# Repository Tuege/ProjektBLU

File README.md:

## Welcome to GitHub Pages

You can use the [editor on GitHub](https://github.com/Tuege/ProjektBLU/edit/master/README.md) to maintain and preview the content for your website in Markdown files.

Whenever you commit to this repository, GitHub Pages will run [Jekyll](https://jekyllrb.com/) to rebuild the pages in your site, from the content in your Markdown files.

### Markdown

Markdown is a lightweight and easy-to-use syntax for styling your writing. It includes conventions for

```markdown
Syntax highlighted code block

# Header 1
## Header 2
### Header 3

- Bulleted
- List

1. Numbered
2. List

**Bold** and _Italic_ and `Code` text

[Link](url) and 
```

For more details see [GitHub Flavored Markdown](https://guides.github.com/features/mastering-markdown/).

### Jekyll Themes

Your Pages site will use the layout and styles from the Jekyll theme you have selected in your [repository settings](https://github.com/Tuege/ProjektBLU/settings). The name of this theme is saved in the Jekyll `_config.yml` configuration file.

### Support or Contact

Having trouble with Pages? Check out our [documentation](https://help.github.com/categories/github-pages-basics/) or [contact support](https://github.com/contact) and we’ll help you sort it out.

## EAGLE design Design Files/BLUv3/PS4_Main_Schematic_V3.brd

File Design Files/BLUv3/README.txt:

This Folder contains the Design files and technical documentation for the BLUv3

This board has been designed to replace the JDM-055 in the PS4 controller and can be programmed using Atmel Studio.
The microcontroller on this board is an ATxmega128A1U and the board also features an integrated esp32 module.

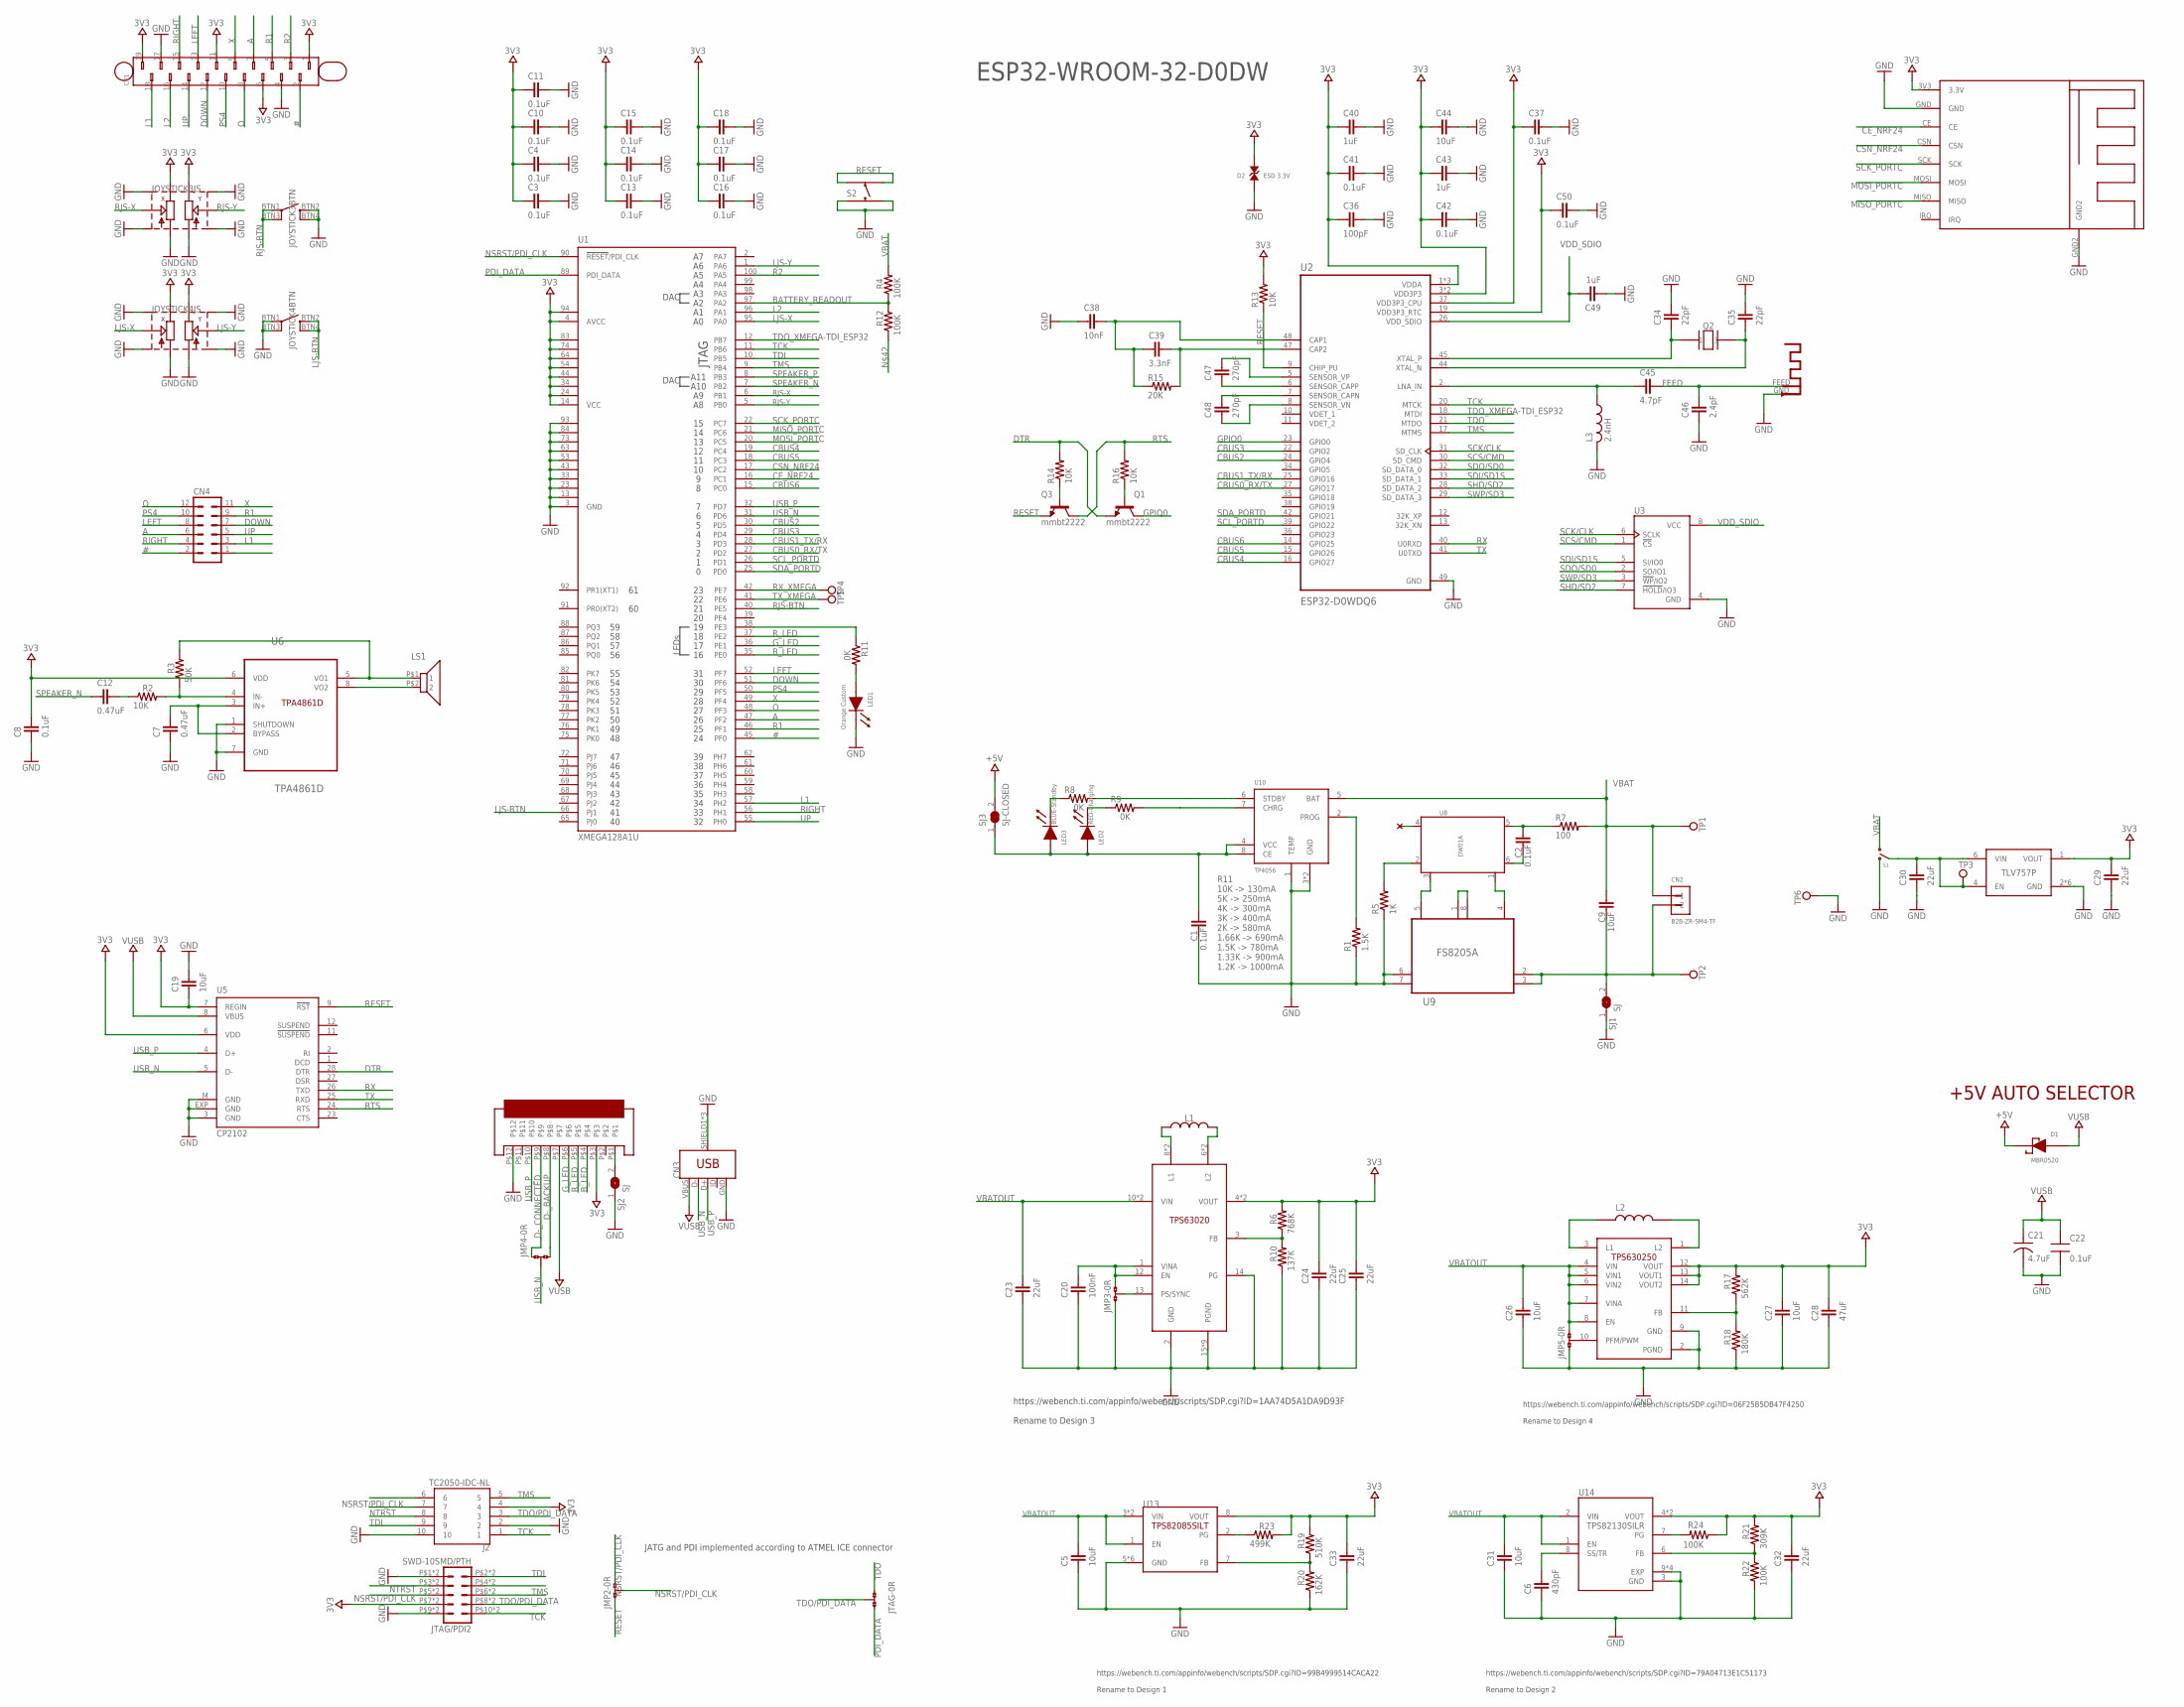
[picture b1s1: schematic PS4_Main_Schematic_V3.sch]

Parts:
ANT1: ESP32-ANTENNA; ESP32-ANT
C1: 0.1uF; C0402
C2: 0.1uF; C0603
C3, C4, C10, C11, C13, C14, C15, C16, C17, C18, C37, C41, C42, C50: 0.1uF; CAPC1005X60N
C5, C19, C26, C27, C31, C44: 10uF; CAPC1608X85N
C6: 430pF; CAPC1608X85N
C7, C12: 0.47uF; CAPC1608X85N
C8: 0.1uF; CAPC1608X85N
C9: 10uF; C0603
C20: 100nF; CAPC1608X85N
C21: 4.7uF; TAN-A
C22: 0.1uF; CAP0805-NP
C23, C24, C25, C29, C30, C32, C33: 22uF; CAPC1608X85N
C28: 47uF; 0805
C34, C35: 22pF; CAPC1005X60N
C36: 100pF; CAPC1005X60N
C38: 10nF; CAPC1005X60N
C39: 3.3nF; CAPC1005X60N
C40, C43, C49: 1uF; CAPC1005X60N
C45: 4.7pF; CAPC1005X60N
C46: 2.4pF; CAPC1005X60N
C47, C48: 270pF; CAPC1005X60N
CN1: 505278-1233; FFC-12-VERTICAL
CN2: B2B-ZR-SM4-TF; B2B-SM
CN3: USB_MICRO-B_REDUCED-OVERHANG; USB-B-MICRO-SMD-RED-OVERHANG
CN4: MA05-2
CP1: CARBON-CONTACTS-JDM055; CARBON-PADS-JDM055
D1: MBR0520; SOD-123
D2: ESD 3.3V; DFN100X60X45-2N
J2: TC2050-IDC-NL; TAG-CONNECT_TC2050-IDC-NL
JMP2, JMP3, JMP4, JMP5: 0R-JUMPC; C0R-JMP
JOYSTICK3, JOYSTICK4: RKJXV1224002RKJXV1224002; RKJXV1224
JTAG: 0R-JUMPC; C0R-JMP
JTAG/PDI2: SWD-10SMD/PTH; M50-3600542
L1: SDR0403-1R0ML; IND_SDR0403-221KL
L2: INDUCTOR_XFL4020-102MEB; IND_XFL4020-102MEB
L3: 2.4nH; INDC1005X45
LED1: Orange Custom; LED0805
LED2: RED-Charging; LED0805
LED3: BLUE-Standby; LED0805
LS1: SPEAKER-CONNECTORS-JDM055
Q1, Q3: mmbt2222; SOT23-3
Q2: OSCCC320X250X60N
R1: 1.5K; R0603
R2, R13, R14, R16: 10K; CAPC1608X85N
R3: 50K; CAPC1608X85N
R4, R12, R22, R24: 100K; CAPC1608X85N
R5: 1K; R0603
R6: 768K; CAPC1005X60N
R7: 100; R0603
R8, R9, R11: 0K; R0603
R10: 137K; CAPC1005X60N
R15: 20K; 603-AC0402FR-0720KL
R17: 562K; CAPC1608X85N
R18: 180K; CAPC1608X85N
R19: 510K; CAPC1608X85N
R20: 162K; CAPC1608X85N
R21: 309K; CAPC1608X85N
R23: 499K; CAPC1608X85N
S1: SSAJ110100
S2: ULTRA-THIN-TACT-SWITCHPTS540; PTS540
SJ1, SJ2: SJ
SJ3: SJ-CLOSED
TP1, TP2, TP3, TP4, TP5, TP6: TP
U1: XMEGA128A1U; TQFP100
U2: ESP32-D0WDQ6; QFN35P500X500X90-49N
U3: GD25Q32CSIGR; SOIC127P790X216-8N
U4: NRF24MINI
U5: CP2102; MLP28
U6: TPA4861D; SOIC127P600X175-8N
U8: DW01A; SOT95P285X140-6N
U9: FS8205A; SOP65P640X120-8N
U10: TP4056; SOP-8
U11: TPS63020; QFN14-3X4MM
U12: TPS630250RNCT; TPS630250
U13: TPS82085SILT8-MICRO_SIP; SON65P280X300X133-9N
U14: TPS82130SILR; PSON65P300X280X153-9N
U$2: LDO-3V3WSON; SON65P200X200X80-7N

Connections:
3V3: C3.2, C4.2, C8.1, C10.2, C11.2, C13.2, C14.2, C15.2, C16.2, C17.2, C18.2, C19.2, C24.1, C25.1, C27.1, C28.1, C29.1, C32.1, C33.1, C36.2, C37.2, C40.2, C41.2, C42.2, C43.2, C44.2, C50.2, CN1.P$3, CP1.1 (D1), CP1.6 (D6), CP1.11 (D11), CP1.19 (D19), D2.2, J2.4, JOYSTICK3.X3, JOYSTICK3.Y3, JOYSTICK4.X3, JOYSTICK4.Y3, JTAG/PDI2.P$7 (7), JTAG/PDI2.P$7_1 (7), R6.2, R13.2, R17.2, R19.2, R21.2, R23.2, R24.1, U1.4 (AVCC), U1.14 (VCC), U1.24 (VCC1), U1.34 (VCC2), U1.44 (VCC3), U1.54 (VCC4), U1.64 (VCC5), U1.74 (VCC6), U1.83 (VCC7), U1.94 (AVCC1), U2.1 (VDDA), U2.3 (VDD3P3), U2.4 (VDD3P3), U2.19 (VDD3P3_RTC), U2.37 (VDD3P3_CPU), U2.43 (VDDA), U2.46 (VDDA), U4.3V3 (3.3V), U5.6 (VDD), U5.7 (REGIN), U6.6 (VDD), U11.4 (VOUT), U11.5 (VOUT), U12.12 (VOUT), U12.13 (VOUT1), U12.14 (VOUT2), U13.8 (VOUT), U14.4 (VOUT), U14.5 (VOUT), U$2.1 (VOUT)
#: CN4.2, CP1.2 (D2), U1.45 (PF0)
+5V: D1.1 (CA), SJ3.2
A: CN4.6, CP1.7 (D7), U1.47 (PF2)
BATTERY_READOUT: R4.1, R12.2, U1.97 (PA2)
B_LED: CN1.P$4, U1.35 (PE0)
CBUS0_RX/TX: U1.27 (PD2), U2.27 (GPIO17)
CBUS1_TX/RX: U1.28 (PD3), U2.25 (GPIO16)
CBUS2: U1.30 (PD5), U2.24 (GPIO4)
CBUS3: U1.29 (PD4), U2.22 (GPIO2)
CBUS4: U1.19 (PC4), U2.16 (GPIO27)
CBUS5: U1.18 (PC3), U2.15 (GPIO26)
CBUS6: U1.15 (PC0), U2.14 (GPIO25)
CE_NRF24: U1.16 (PC1), U4.CE
CSN_NRF24: U1.17 (PC2), U4.CSN
D-_BACKUP: CN1.P$8, JMP4.1
D-_CONNECTED: CN1.P$9, JMP4.3
DOWN: CN4.7, CP1.12 (D12), U1.51 (PF6)
DTR: Q1.2 (E), R14.2, U5.28 (DTR)
FEED: ANT1.FEED, C45.1, C46.1
GND: ANT1.GND, C1.2, C3.1, C4.1, C5.2, C6.2, C7.2, C8.2, C10.1, C11.1, C13.1, C14.1, C15.1, C16.1, C17.1, C18.1, C19.1, C20.2, C21.2, C22.2, C23.2, C24.2, C25.2, C26.2, C27.2, C28.2, C29.2, C30.2, C31.2, C32.2, C33.2, C34.1, C35.1, C36.1, C37.1, C38.2, C40.1, C41.1, C42.1, C43.1, C44.1, C46.2, C49.2, C50.1, CN1.GND1 (GND), CN1.GND2 (GND), CN1.GND3 (GND), CN1.GND4 (GND), CN1.P$12, CN3.GND, CN3.SHIELD1 (SHIELD), CN3.SHIELD2 (SHIELD), CN3.SHIELD3 (SHIELD), CP1.4 (D4), CP1.17 (D17), D2.1, J2.2, J2.10, JMP3.3, JMP5.3, JOYSTICK3.BTN2 (2), JOYSTICK3.BTN4 (4), JOYSTICK3.CASE1, JOYSTICK3.CASE2, JOYSTICK3.CASE3, JOYSTICK3.CASE4, JOYSTICK3.X1, JOYSTICK3.Y1, JOYSTICK4.BTN1 (1), JOYSTICK4.BTN3 (3), JOYSTICK4.CASE1, JOYSTICK4.CASE2, JOYSTICK4.CASE3, JOYSTICK4.CASE4, JOYSTICK4.X1, JOYSTICK4.Y1, JTAG/PDI2.P$1 (1), JTAG/PDI2.P$1_1 (1), JTAG/PDI2.P$9 (9), JTAG/PDI2.P$9_1 (9), L3.2, LED1.1 (CA), Q2.2 (GND), Q2.4 (GND), R1.1, R5.1, R10.1, R18.1, R20.1, R22.1, S1.1 (A), S2.3, S2.4, SJ1.1, SJ2.1, TP6.TP, U1.3 (GND), U1.13 (GND1), U1.23 (GND2), U1.33 (GND3), U1.43 (GND4), U1.53 (GND5), U1.63 (GND6), U1.73 (GND7), U1.84 (GND8), U1.93 (GND9), U2.49 (GND), U3.4 (GND), U4.GND, U4.GND2, U5.3 (GND), U5.EXP (GND), U5.M (GND), U6.1 (SHUTDOWN), U6.7 (GND), U9.6, U9.7, U10.1 (TEMP), U10.3 (GND), U10.9 (GND), U11.2 (GND), U11.14 (PG), U11.15 (PGND), U11.16 (PGND), U11.17 (PGND), U11.18 (PGND), U11.19 (PGND), U11.20 (PGND), U11.21 (PGND), U11.22 (PGND), U11.23 (PGND), U12.2 (PGND), U12.9 (GND), U13.5 (GND), U13.6 (GND), U13.9 (GND), U13.P$1 (GND), U13.P$2 (GND), U13.P$3 (GND), U14.3 (GND), U14.9 (EXP), U14.9_1 (EXP), U14.9_2 (EXP), U14.9_3 (EXP), U$2.2 (GND), U$2.3 (GND), U$2.5 (GND), U$2.7 (GND), U$2.7_1 (GND), U$2.7_2 (GND)
GPIO0: Q1.3 (C), U2.23 (GPIO0)
G_LED: CN1.P$6, U1.36 (PE1)
L1: CN4.3, CP1.18 (D18), U1.57 (PH2)
L2: CP1.16 (D16), U1.96 (PA1)
LEFT: CN4.8, CP1.13 (D13), U1.52 (PF7)
LJS-BTN: JOYSTICK4.BTN2 (2), JOYSTICK4.BTN4 (4), U1.66 (PJ1)
LJS-X: JOYSTICK4.X2, U1.95 (PA0)
LJS-Y: JOYSTICK4.Y2, U1.1 (PA6)
MISO_PORTC: U1.21 (PC6), U4.MISO
MOSI_PORTC: U1.20 (PC5), U4.MOSI
unnamed: L1.1, U11.8 (L1), U11.9 (L1)
unnamed: C12.1, R2.1
unnamed: R2.2, R3.1, U6.4 (IN-)
unnamed: L1.2, U11.6 (L2), U11.7 (L2)
unnamed: R5.2, U8.2
unnamed: C2.1, R7.1, U8.5
unnamed: U8.3, U9.5
unnamed: U8.1, U9.4
unnamed: JTAG/PDI2.P$4 (4), JTAG/PDI2.P$4_1 (4)
unnamed: C2.2, U8.6
unnamed: C9.2, CN2.P$2 (2), R12.1, SJ1.2, TP2.TP, U9.2, U9.3
unnamed: U9.1, U9.8
unnamed: R1.2, U10.2 (PROG)
unnamed: LED2.1 (CA), R9.1
unnamed: LED3.1 (CA), R8.1
unnamed: R9.2, U10.7 (CHRG)
unnamed: R8.2, U10.6 (STDBY)
unnamed: C1.1, LED2.2 (AN), LED3.2 (AN), SJ3.1, U10.4 (VCC), U10.8 (CE)
unnamed: CN1.P$1, SJ2.2
unnamed: Q1.1 (B), R16.1
unnamed: Q3.1 (B), R14.1
unnamed: L2.1, U12.3 (L1)
unnamed: JMP3.2, U11.13 (PS/SYNC)
unnamed: R11.1, U1.38 (PE3)
unnamed: LED1.2 (AN), R11.2
unnamed: R19.1, R20.2, U13.7 (FB)
unnamed: R6.1, R10.2, U11.3 (FB)
unnamed: L2.2, U12.1 (L2)
unnamed: C20.1, JMP3.1, U11.1 (VINA), U11.12 (EN)
unnamed: LS1.P$2 (2), U6.8 (VO2)
unnamed: LS1.P$1 (1), R3.2, U6.5 (VO1)
unnamed: R21.1, R22.2, U14.6 (FB)
unnamed: R17.1, R18.2, U12.11 (FB)
unnamed: R23.1, U13.2 (PG)
unnamed: R24.2, U14.7 (PG)
unnamed: JMP5.2, U12.10 (PFM/PWM)
unnamed: C6.1, U14.8 (SS/TR)
unnamed: C34.2, Q2.1, U2.45 (XTAL_P)
unnamed: C35.2, Q2.3, U2.44 (XTAL_N)
unnamed: C45.2, L3.1, U2.2 (LNA_IN)
unnamed: C48.1, U2.7 (SENSOR_CAPN)
unnamed: C47.2, U2.6 (SENSOR_CAPP)
unnamed: C47.1, U2.5 (SENSOR_VP)
unnamed: C48.2, U2.8 (SENSOR_VN)
unnamed: C39.1, R15.2, U2.47 (CAP2)
unnamed: C38.1, C39.2, R15.1, U2.48 (CAP1)
NSRST/PDI_CLK: J2.7, JMP2.1, JMP2.2, JTAG/PDI2.P$5 (5), JTAG/PDI2.P$5_1 (5), U1.90 (!RESET!/PDI_CLK)
NTRST: J2.8, JTAG/PDI2.P$3 (3), JTAG/PDI2.P$3_1 (3)
O: CN4.12, CP1.8 (D8), U1.48 (PF3)
PDI_DATA: JTAG.1, U1.89 (PDI_DATA)
PS4: CN4.10, CP1.10 (D10), U1.50 (PF5)
R1: CN4.9, CP1.5 (D5), U1.46 (PF1)
R2: CP1.3 (D3), U1.100 (PA5)
RESET: JMP2.3, Q3.2 (E), R13.1, S2.1, S2.2, U2.9 (CHIP_PU), U5.9 (!RST)
RIGHT: CN4.4, CP1.15 (D15), U1.56 (PH1)
RJS-BTN: JOYSTICK3.BTN1 (1), JOYSTICK3.BTN3 (3), U1.40 (PE5)
RJS-X: JOYSTICK3.X2, U1.6 (PB1)
RJS-Y: JOYSTICK3.Y2, U1.5 (PB0)
RTS: Q3.3 (C), R16.2, U5.24 (RTS)
RX: U2.40 (U0RXD), U5.26 (TXD)
RX_XMEGA: TP4.TP, U1.42 (PE7)
R_LED: CN1.P$5, U1.37 (PE2)
SCK/CLK: U2.31 (SD_CLK), U3.6 (SCLK)
SCK_PORTC: U1.22 (PC7), U4.SCK
SCL_PORTD: U1.26 (PD1), U2.39 (GPIO22)
SCS/CMD: U2.30 (SD_CMD), U3.1 (!CS)
SDA_PORTD: U1.25 (PD0), U2.42 (GPIO21)
SDI/SD1S: U2.33 (SD_DATA_1), U3.5 (SI/IO0)
SDO/SD0: U2.32 (SD_DATA_0), U3.2 (SO/IO1)
SHD/SD2: U2.28 (SD_DATA_2), U3.7 (!HOLD!/IO3)
SPEAKER_N: C12.2, U1.7 (PB2)
SPEAKER_P: C7.1, U1.8 (PB3), U6.2 (BYPASS), U6.3 (IN+)
SWP/SD3: U2.29 (SD_DATA_3), U3.3 (!WP!/IO2)
TCK: J2.1, JTAG/PDI2.P10_1 (10), JTAG/PDI2.P$10 (10), U1.11 (PB6), U2.20 (MTCK)
TDI: J2.9, JTAG/PDI2.P$2 (2), JTAG/PDI2.P$2_1 (2), U1.10 (PB5)
TDO: JTAG.3, U2.21 (MTDO)
TDO/PDI_DATA: J2.3, JTAG.2, JTAG/PDI2.P$8 (8), JTAG/PDI2.P$8_1 (8)
TDO_XMEGA-TDI_ESP32: U1.12 (PB7), U2.18 (MTDI)
TMS: J2.5, JTAG/PDI2.P$6 (6), JTAG/PDI2.P$6_1 (6), U1.9 (PB4), U2.17 (MTMS)
TX: U2.41 (U0TXD), U5.25 (RXD)
TX_XMEGA: TP5.TP, U1.41 (PE6)
UP: CN4.5, CP1.14 (D14), U1.55 (PH0)
USB_N: CN3.D-, JMP4.2, U1.31 (PD6), U5.5 (D-)
USB_P: CN1.P$10, CN3.D+, U1.32 (PD7), U5.4 (D+)
VBAT: C9.1, CN2.P$1 (1), R4.2, R7.2, S1.2 (B), TP1.TP, U10.5 (BAT)
VBATOUT: C5.1, C23.1, C26.1, C30.1, C31.1, JMP5.1, S1.C (COM), TP3.TP, U11.10 (VIN), U11.11 (VIN), U12.4 (VIN), U12.5 (VIN1), U12.6 (VIN2), U12.7 (VINA), U12.8 (EN), U13.1 (EN), U13.3 (VIN), U13.4 (VIN), U14.1 (EN), U14.2 (VIN), U$2.4 (EN), U$2.6 (VIN)
VDD_SDIO: C49.1, U2.26 (VDD_SDIO), U3.8 (VCC)
VUSB: C21.1, C22.1, CN1.P$7, CN3.VBUS, D1.2 (AN), U5.8 (VBUS)
X: CN4.11, CP1.9 (D9), U1.49 (PF4)

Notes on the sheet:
+5V AUTO SELECTOR
R11 10K -> 130mA 5K -> 250mA 4K -> 300mA 3K -> 400mA 2K -> 580mA 1.66K -> 690mA 1.5K -> 780mA 1.33K -> 900mA 1.2K -> 1000mA
ESP32-WROOM-32-D0DW
JTAG
JATG and PDI implemented according to ATMEL ICE connector
LEDs
DAC
https://webench.ti.com/appinfo/webench/scripts/SDP.cgi?ID=1AA74D5A1DA9D93F Rename to Design 3
https://webench.ti.com/appinfo/webench/scripts/SDP.cgi?ID=06F25B5DB47F4250 Rename to Design 4
https://webench.ti.com/appinfo/webench/scripts/SDP.cgi?ID=79A04713E1C51173 Rename to Design 2
https://webench.ti.com/appinfo/webench/scripts/SDP.cgi?ID=99B4999514CACA22 Rename to Design 1

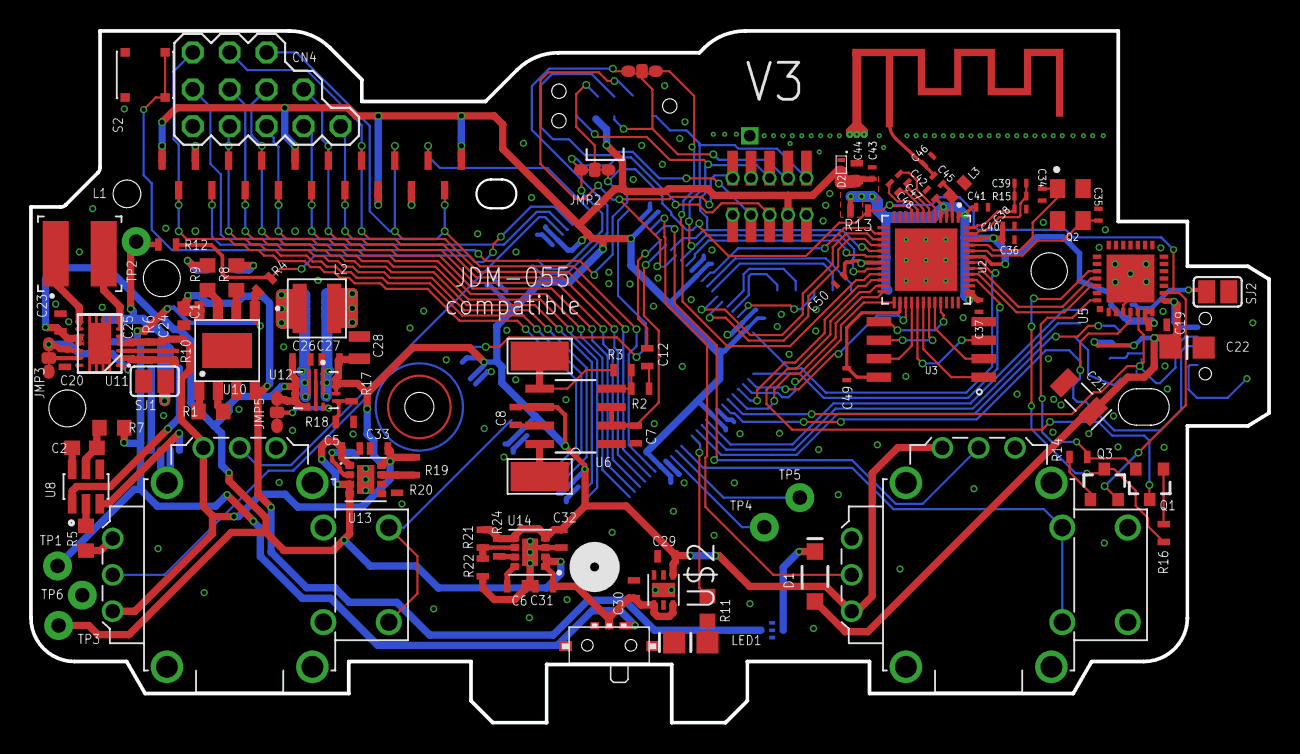
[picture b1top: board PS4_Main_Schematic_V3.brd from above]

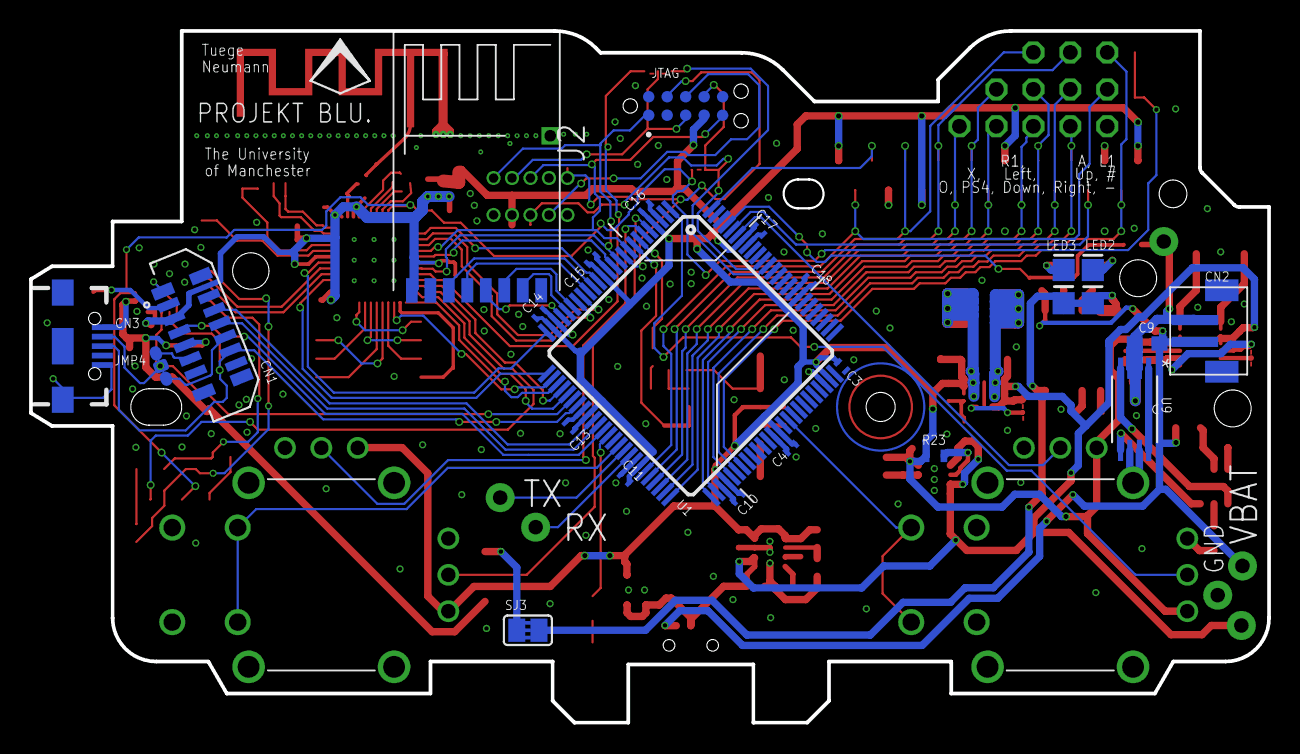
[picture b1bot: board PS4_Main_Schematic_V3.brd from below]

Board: 2 copper layers, 85.1 x 47.5 mm, 126 parts (23 on the bottom side), 120 nets.

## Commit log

2019-10-11 Set theme jekyll-theme-minimal
2019-10-11 Restoring original readme
    Wiki theme overwrote the original readme
2019-10-12 Create boards.txt
    Added board setup for Arduino Pro Mini initially
2019-10-12 Create platform.txt
    Based on Arduino AVR boards Core and platform file
2019-10-12 Update boards.txt
    added missing menu header
2019-10-12 Rename README.md to README.txt
2019-10-12 Update package_ProjektBLU_AVR_boards_index.json
    changed file location and type to zip
2019-10-12 Update package_ProjektBLU_AVR_boards_index.json
    corrected download link
2019-10-12 Update package_ProjektBLU_AVR_boards_index.json
    updated folder structure to conform with Arduino IDE requirements to find boards.txt
2020-04-15 added information on BLUv3
2020-04-15 Add schematic and board layout
2020-04-21 Cleaned up Schematic
2020-04-21 Create BLUv2 directory
2020-04-25 Upload 3D files
2024-02-20 Rename README.txt to README.md

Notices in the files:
parts and their libraries:
SparkFun: Licensing: CC v3.0 Share-Alike You are welcome to use this library for commercial purposes.
